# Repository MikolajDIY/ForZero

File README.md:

# ForZero

Sterownik fizycznego zestawu wskaźników Audi A4 B6, pozwalający wyświetlać telemetrię z Forza Horizon 6 przy użyciu STM32, CAN, USB i autorskiej aplikacji Qt.

ForZero powstał jako próba wykorzystania fizycznego zestawu wskaźników jako elementu stanowiska simracingowego. Projekt obejmuje rozpoznanie sposobów sterowania licznikiem, zaprojektowanie i uruchomienie własnej PCB, firmware mikrokontrolera oraz aplikację komputerową.

## Film prezentujący projekt

[Obejrzyj film na YouTube](https://www.youtube.com/watch?v=puXx0WQHfvw)

## Możliwości

- Wyświetlanie prędkości i obrotów silnika na fizycznym liczniku.
- Sterowanie wskazaniami poziomu paliwa i temperatury płynu chłodzącego.
- Obsługa wybranych kontrolek i komunikatów ostrzegawczych.
- Przybliżona symulacja stanów ABS, TCS i AIRBAG oraz temperatury płynu chłodzącego na podstawie dostępnej telemetrii.
- Odbiór danych UDP z gry i przesyłanie przetworzonych wartości do sterownika przez USB VCP.
- Pomiar opóźnień komunikacji na podstawie potwierdzeń wykonania ramek.
- Zerowanie prędkości i obrotów po 500 ms bez poprawnej ramki danych.

Gra nie udostępnia bezpośrednio wszystkich odwzorowywanych stanów. Algorytmy symulacji kontrolek i temperatury służą do przybliżonego odtworzenia ich zachowania; nie są modelami fizycznymi układów pojazdu.

## Jak to działa

Gra wysyła telemetrię przez UDP. Aplikacja Qt odbiera i parsuje pakiety, wykonuje dodatkową logikę oraz przesyła dane przez USB VCP do STM32F105. Mikrokontroler generuje sygnały elektryczne wymagane przez zestaw wskaźników.

Badany licznik wykorzystuje kilka różnych sposobów sterowania:

| Funkcja | Sposób sterowania |
| --- | --- |
| Obrotomierz | Ramki CAN |
| Prędkościomierz | Sygnał impulsowy o regulowanej częstotliwości |
| Poziom paliwa i temperatura | Emulacja rezystancji czujników |
| Wybrane kontrolki i ostrzeżenia | Sygnały logiczne 12 V |

Wskazania paliwa i temperatury skalibrowano eksperymentalnie. Zmierzone charakterystyki opracowano z wykorzystaniem interpolacji PCHIP w MATLAB-ie.

## Sprzęt

- Autorska dwuwarstwowa PCB zaprojektowana w KiCad.
- Mikrokontroler STM32F105 z jednoczesną obsługą USB i CAN.
- Transceiver CAN MCP2562 z osobnym zasilaniem interfejsu logicznego.
- Układy emulacji rezystancji oparte na potencjometrze cyfrowym MCP4661, wzmacniaczach operacyjnych i tranzystorach MOSFET.
- Tranzystorowe stopnie sterujące wejściami 12 V licznika.
- Złącze USB-C, zewnętrzne zasilanie 12 V i złącza Molex Micro-Fit 3.0.
- Zabezpieczenie ESD linii USB oraz bezpieczniki polimerowe na liniach zasilania.

## Oprogramowanie

### Aplikacja PC — C++ / Qt

Aplikacja ma trzy wątki: GUI, odbiór UDP oraz komunikację USB. Oddzielenie komunikacji od interfejsu użytkownika pozwala odbierać telemetrię i obsługiwać sterownik bez wykonywania tych operacji w wątku GUI.

Aplikacja odpowiada za parsowanie telemetrii, symulację wybranych wskazań, przygotowanie ramek dla sterownika i wyznaczanie statystyk opóźnień.

### Firmware — C / STM32 HAL

Firmware powstał w STM32CubeIDE z wykorzystaniem bibliotek HAL. Zadania w pętli głównej są wyzwalane zdarzeniowo lub w ustalonych interwałach:

| Sygnał | Aktualizacja |
| --- | --- |
| Prędkość i kontrolki | Po otrzymaniu nowych danych, gdy wartość się zmieni |
| Obroty silnika | Ramka CAN co 20 ms |
| Temperatura | Co 2 s |
| Poziom paliwa | Co 5 s, jeżeli odebrano nowe dane |

Własny protokół przesyłany przez USB VCP wykorzystuje znaczniki ramki, CRC8, numer sekwencyjny i potwierdzenie wykonania `Exec Ack`. Parser posiada timeout odbioru, a brak poprawnych danych przez 500 ms powoduje wyzerowanie prędkości i obrotów.

## Opóźnienia

Aplikacja mierzy czas przejścia danych w pętli PC–sterownik–PC (RTT), wykorzystując numery ramek i odpowiadające im potwierdzenia. Statystyki obejmują ostatnie 20 000 pomiarów.

W zestawach pomiarowych opisanych w dokumentacji średnie RTT zazwyczaj wynosiło poniżej 1 ms, a P99 poniżej 4 ms. W najbardziej skrajnym zarejestrowanym zestawie P99 osiągnął 17 ms. Są to wyniki przeprowadzonych testów, a nie gwarantowane limity czasowe.

**RTT nie jest pomiarem czasu od zdarzenia w grze do mechanicznego wychylenia wskazówki.** Poszczególne wyjścia mają własne okresy odświeżania, a licznik dodatkowo filtruje wskazania. Projekt pracuje jako system soft real-time.

## Zawartość repozytorium

| Folder | Zawartość |
| --- | --- |
| [Aplikacja Qt](Aplikacja%20Qt/) | Kod źródłowy aplikacji komputerowej |
| [Oprogramowanie sterownika](Oprogramowanie%20sterownika/) | Projekt firmware mikrokontrolera STM32 |
| [Schematy](Schematy/) | Materiały dotyczące części sprzętowej |
| [Obrazy](Obrazy/) | Zdjęcia i grafiki wykorzystywane w README |
| [Dokumentacja](ForZero_dokumentacja_v1.pdf) | Szczegółowa dokumentacja projektu |

## Uruchomienie

### Wymagania

- Zestaw wskaźników zgodny z egzemplarzem wykorzystanym w projekcie.
- Zmontowany sterownik ForZero, przewody połączeniowe i zasilanie 12 V.
- Przewód USB obsługujący transmisję danych.
- Komputer z aplikacją ForZero oraz Forza Horizon 6.
- Do samodzielnego zbudowania oprogramowania: środowisko Qt z kompilatorem C++ oraz STM32CubeIDE.

### Kolejność czynności

1. Przy odłączonym zasilaniu połącz sterownik z licznikiem zgodnie ze schematem połączeń w dokumentacji. Uwzględnij numerację pinów obu złączy licznika.
2. Zbuduj firmware z folderu [Oprogramowanie sterownika](Oprogramowanie%20sterownika/) i wgraj go do STM32. Programowanie jest możliwe przez USB z wykorzystaniem wbudowanego bootloadera.
3. Aby wejść w tryb bootloadera: naciśnij RESET, przytrzymując go naciśnij BOOT, zwolnij RESET, a następnie BOOT.
4. Po zaprogramowaniu uruchom sterownik w zwykłym trybie pracy i podłącz zasilanie zestawu.
5. Zbuduj i uruchom aplikację z folderu [Aplikacja Qt](Aplikacja%20Qt/), a następnie wybierz port COM sterownika.
6. Włącz wysyłanie telemetrii UDP w grze. Ustaw adres IP komputera odbierającego dane oraz port zgodny z konfiguracją aplikacji.
7. Uruchom jazdę i sprawdź odbiór danych oraz działanie wskazań.

<!-- Do uzupełnienia przed publikacją: sprawdzone wersje Qt i kompilatora, wymagane moduły Qt, dokładna procedura budowania, narzędzie do wgrywania przez USB oraz ustawienia telemetrii (IP, port i format pakietu). -->

## Zgodność i ograniczenia

- Projekt sprawdzono z licznikiem **Audi A4 B6 RB4 o oznaczeniu 8E0920900H**, z monochromatycznym wyświetlaczem FIS. Zgodność z innymi wersjami licznika nie została potwierdzona.
- W badanym egzemplarzu po rozpoczęciu jazdy wskazanie paliwa zmieniało się wyłącznie w dół, z tempem około jednej czwartej skali w ciągu 7–10 minut. Ograniczenie to utrudnia szybkie odwzorowanie zmian poziomu paliwa w grze.
- Kontrolki i komunikaty mają zachowanie wynikające z wewnętrznej logiki licznika. Symulacja ABS nie oznacza pełnej emulacji sterownika ABS ani niezależnego sterowania samą lampką ABS.
- Poziom 12 V dla wybranych wejść kontrolek przyjęto na podstawie testów używanego egzemplarza; nie potwierdzono go dokumentacją producenta.

## Dokumentacja

Dokumentacja projektu opisuje pinout licznika, schemat połączeń ze sterownikiem, układy elektroniczne, kalibrację wskazań, protokół USB oraz przeprowadzone testy.

<!-- Do uzupełnienia: dodaj względny link do PDF-u po ustaleniu jego nazwy i lokalizacji w repozytorium. -->

## Autor

M.Ratajczak — [MikolajDIY](https://github.com/MikolajDIY)

<!-- Przed publikacją określ zasady licencjonowania własnego kodu i projektu sprzętu. Zachowaj informacje licencyjne zależności i kodu generowanego. Dodaj odnośniki do wykorzystanych materiałów zewnętrznych. -->

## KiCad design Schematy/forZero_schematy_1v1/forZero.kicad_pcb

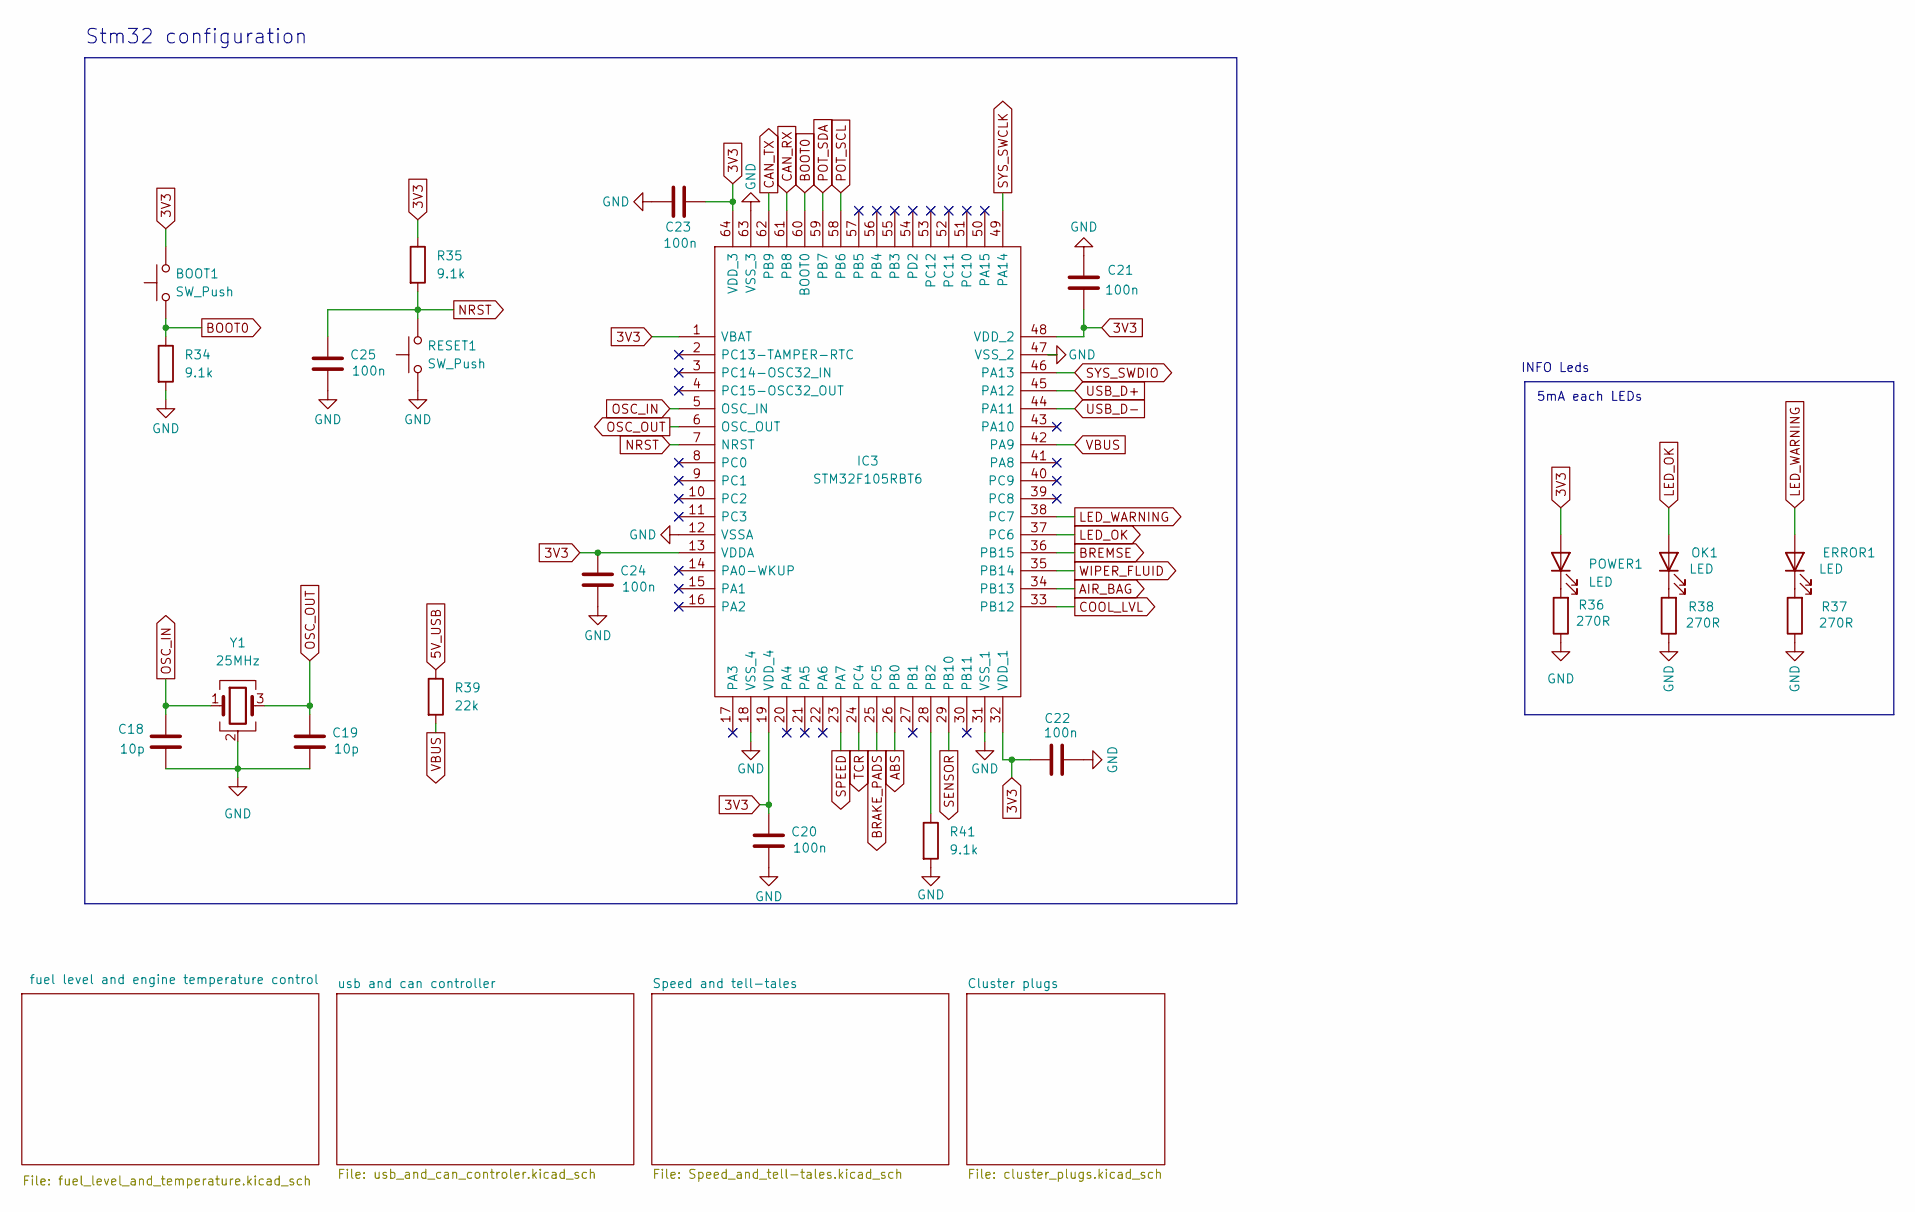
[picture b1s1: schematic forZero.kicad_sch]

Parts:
BOOT1: SW_Push; SW_SPST_PTS645Sx43SMTR92
C18, C19: 10p; C_0805_2012Metric_Pad1.18x1.45mm_HandSolder
C20, C21, C22, C23, C24, C25: 100n; C_0805_2012Metric_Pad1.18x1.45mm_HandSolder
ERROR1: LED; LED_0603_1608Metric_Pad1.05x0.95mm_HandSolder
IC3: STM32F105RBT6; QFP50P1200X1200X160-64N; Mouser Part Number 511-STM32F105RBT6
OK1: LED; LED_0603_1608Metric_Pad1.05x0.95mm_HandSolder
POWER1: LED; LED_0603_1608Metric_Pad1.05x0.95mm_HandSolder
R34, R35, R41: 9.1k; R_0805_2012Metric_Pad1.20x1.40mm_HandSolder
R36, R37, R38: 270R; R_0805_2012Metric_Pad1.20x1.40mm_HandSolder
R39: 22k; R_0805_2012Metric_Pad1.20x1.40mm_HandSolder
RESET1: SW_Push; SW_SPST_PTS645Sx43SMTR92
Y1: 25MHz; Crystal_SMD_3225-4Pin_3.2x2.5mm

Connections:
3V3: BOOT1.2, C20.1, C21.1, C22.1, C23.1, C24.1, IC3.1 (VBAT), IC3.13 (VDDA), IC3.19 (VDD_4), IC3.32 (VDD_1), IC3.48 (VDD_2), IC3.64 (VDD_3), POWER1.2 (A), R35.1; also elsewhere on the board
5V: R39.1; also elsewhere on the board
ABS: IC3.26 (PB0); also elsewhere on the board
AIR_BAG: IC3.34 (PB13); also elsewhere on the board
BOOT0: BOOT1.1, IC3.60 (BOOT0), R34.1; also elsewhere on the board
BRAKE_PADS: IC3.25 (PC5); also elsewhere on the board
BREMSE: IC3.36 (PB15); also elsewhere on the board
CAN_RX: IC3.61 (PB8); also elsewhere on the board
CAN_TX: IC3.62 (PB9); also elsewhere on the board
COOL_LVL: IC3.33 (PB12); also elsewhere on the board
GND: C18.2, C19.2, C20.2, C21.2, C22.2, C23.2, C24.2, C25.2, IC3.12 (VSSA), IC3.18 (VSS_4), IC3.31 (VSS_1), IC3.47 (VSS_2), IC3.63 (VSS_3), R34.2, R36.1, R37.1, R38.1, R41.2, RESET1.1, Y1.2 (G), Y1.4 (G); also elsewhere on the board
LED_OK: IC3.37 (PC6), OK1.2 (A); also elsewhere on the board
LED_WARNING: ERROR1.2 (A), IC3.38 (PC7); also elsewhere on the board
NRST: C25.1, IC3.7 (NRST), R35.2, RESET1.2; also elsewhere on the board
unnamed 33: ERROR1.1 (K), R37.2; also elsewhere on the board
unnamed: IC3.28 (PB2), R41.1
unnamed 46: OK1.1 (K), R38.2; also elsewhere on the board
unnamed 47: POWER1.1 (K), R36.2; also elsewhere on the board
OSC_IN: C18.1, IC3.5 (OSC_IN), Y1.1
OSC_OUT: C19.1, IC3.6 (OSC_OUT), Y1.3
POT_SCL: IC3.58 (PB6); also elsewhere on the board
POT_SDA: IC3.59 (PB7); also elsewhere on the board
SENSOR: IC3.29 (PB10); also elsewhere on the board
SPEED: IC3.23 (PA7); also elsewhere on the board
SYS_SWCLK: IC3.49 (PA14)
SYS_SWDIO: IC3.46 (PA13)
TCR: IC3.24 (PC4); also elsewhere on the board
USB_D+: IC3.45 (PA12); also elsewhere on the board
USB_D-: IC3.44 (PA11); also elsewhere on the board
VBUS: IC3.42 (PA9), R39.2
WIPER_FLUID: IC3.35 (PB14); also elsewhere on the board

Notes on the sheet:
INFO Leds
5mA each LEDs
Stm32 configuration

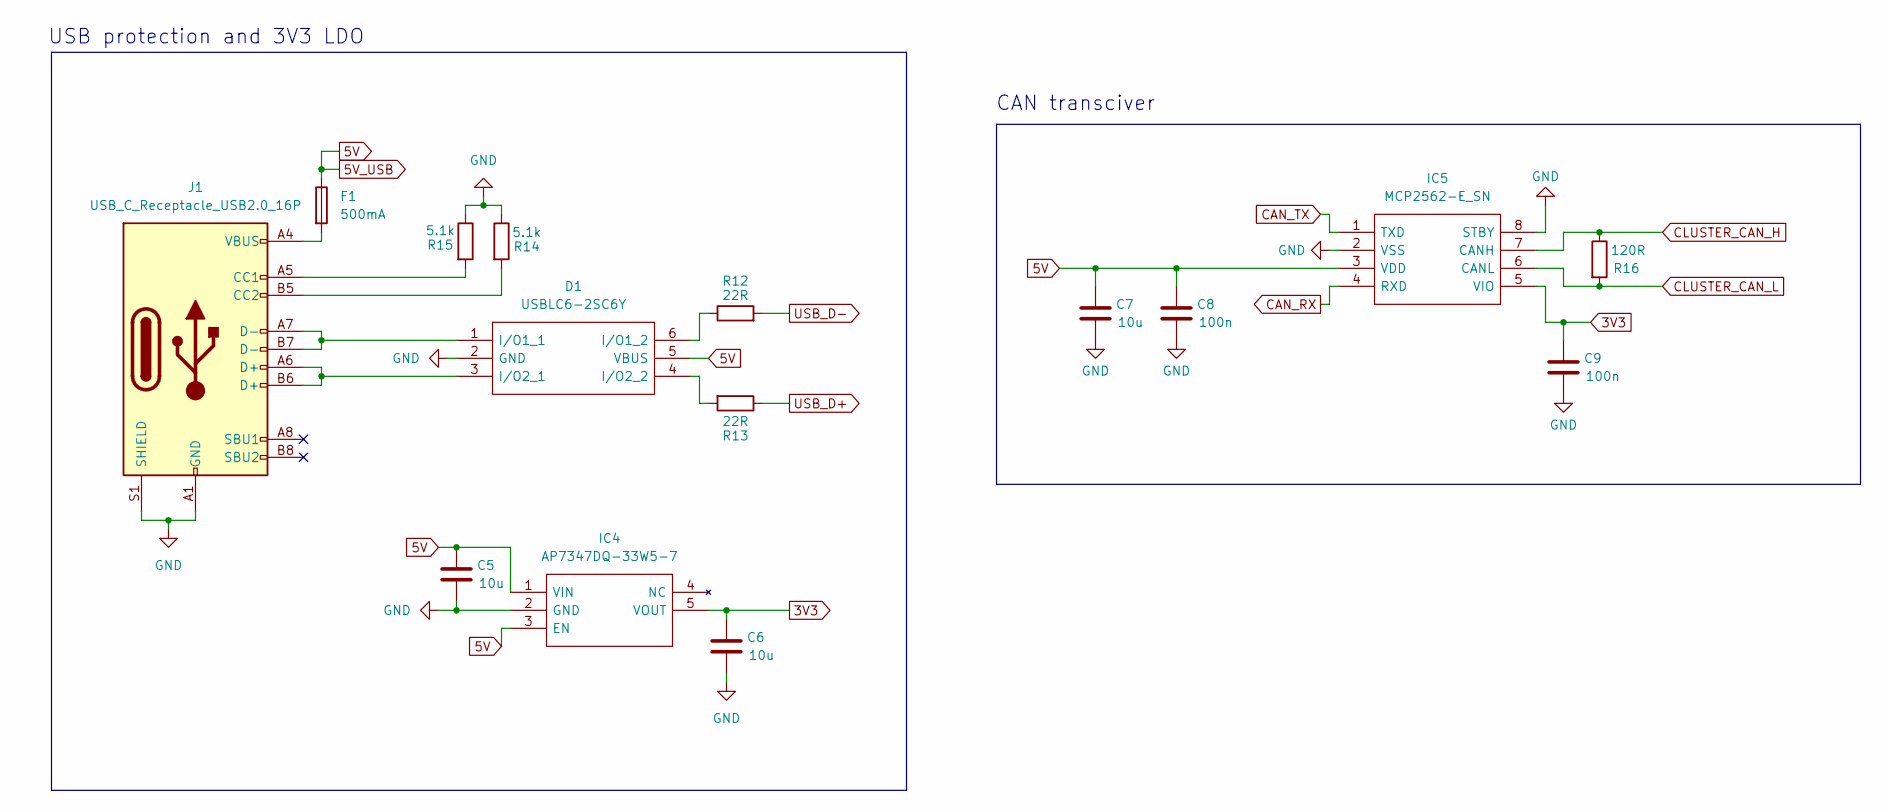
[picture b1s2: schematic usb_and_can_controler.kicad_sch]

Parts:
C5, C6, C7: 10u; C_0805_2012Metric_Pad1.18x1.45mm_HandSolder
C8, C9: 100n; C_0805_2012Metric_Pad1.18x1.45mm_HandSolder
D1: USBLC6-2SC6Y; SOT95P280X145-6N; Mouser Part Number 511-USBLC6-2SC6Y
F1: 500mA; Fuse_1206_3216Metric_Pad1.42x1.75mm_HandSolder
IC4: AP7347DQ-33W5-7; SOT95P280X145-5N; Mouser Part Number 621-AP7347DQ-33W5-7
IC5: MCP2562-E_SN; SOIC127P600X175-8N; Mouser Part Number 579-MCP2562-E/SN
J1: USB_C_Receptacle_USB2.0_16P; USB_C_Receptacle_GCT_USB4105-xx-A_16P_TopMnt_Horizontal
R12, R13: 22R; R_0805_2012Metric_Pad1.20x1.40mm_HandSolder
R14, R15: 5.1k; R_0805_2012Metric_Pad1.20x1.40mm_HandSolder
R16: 120R; R_0805_2012Metric_Pad1.20x1.40mm_HandSolder

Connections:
3V3: C6.1, C9.1, IC4.5 (VOUT), IC5.5 (VIO); also elsewhere on the board
5V: C5.1, C7.1, C8.1, D1.5 (VBUS), F1.1, IC4.1 (VIN), IC4.3 (EN), IC5.3 (VDD); also elsewhere on the board
CAN_RX: IC5.4 (RXD); also elsewhere on the board
CAN_TX: IC5.1 (TXD); also elsewhere on the board
CLUSTER_CAN_H: IC5.7 (CANH), R16.1; also elsewhere on the board
CLUSTER_CAN_L: IC5.6 (CANL), R16.2; also elsewhere on the board
GND: C5.2, C6.2, C7.2, C8.2, C9.2, D1.2 (GND), IC4.2 (GND), IC5.2 (VSS), IC5.8 (STBY), J1.A1 (GND), J1.A12 (GND), J1.B1 (GND), J1.B12 (GND), J1.S1 (SHIELD), R14.1, R15.1; also elsewhere on the board
unnamed: D1.1 (I/O1_1), J1.A7 (D-), J1.B7 (D-)
unnamed: D1.6 (I/O1_2), R12.1
unnamed: D1.3 (I/O2_1), J1.A6 (D+), J1.B6 (D+)
unnamed: D1.4 (I/O2_2), R13.2
unnamed: F1.2, J1.A4 (VBUS), J1.A9 (VBUS), J1.B4 (VBUS), J1.B9 (VBUS)
unnamed: J1.A5 (CC1), R15.2
unnamed: J1.B5 (CC2), R14.2
USB_D+: R13.1; also elsewhere on the board
USB_D-: R12.2; also elsewhere on the board

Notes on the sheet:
CAN transciver
USB protection and 3V3 LDO

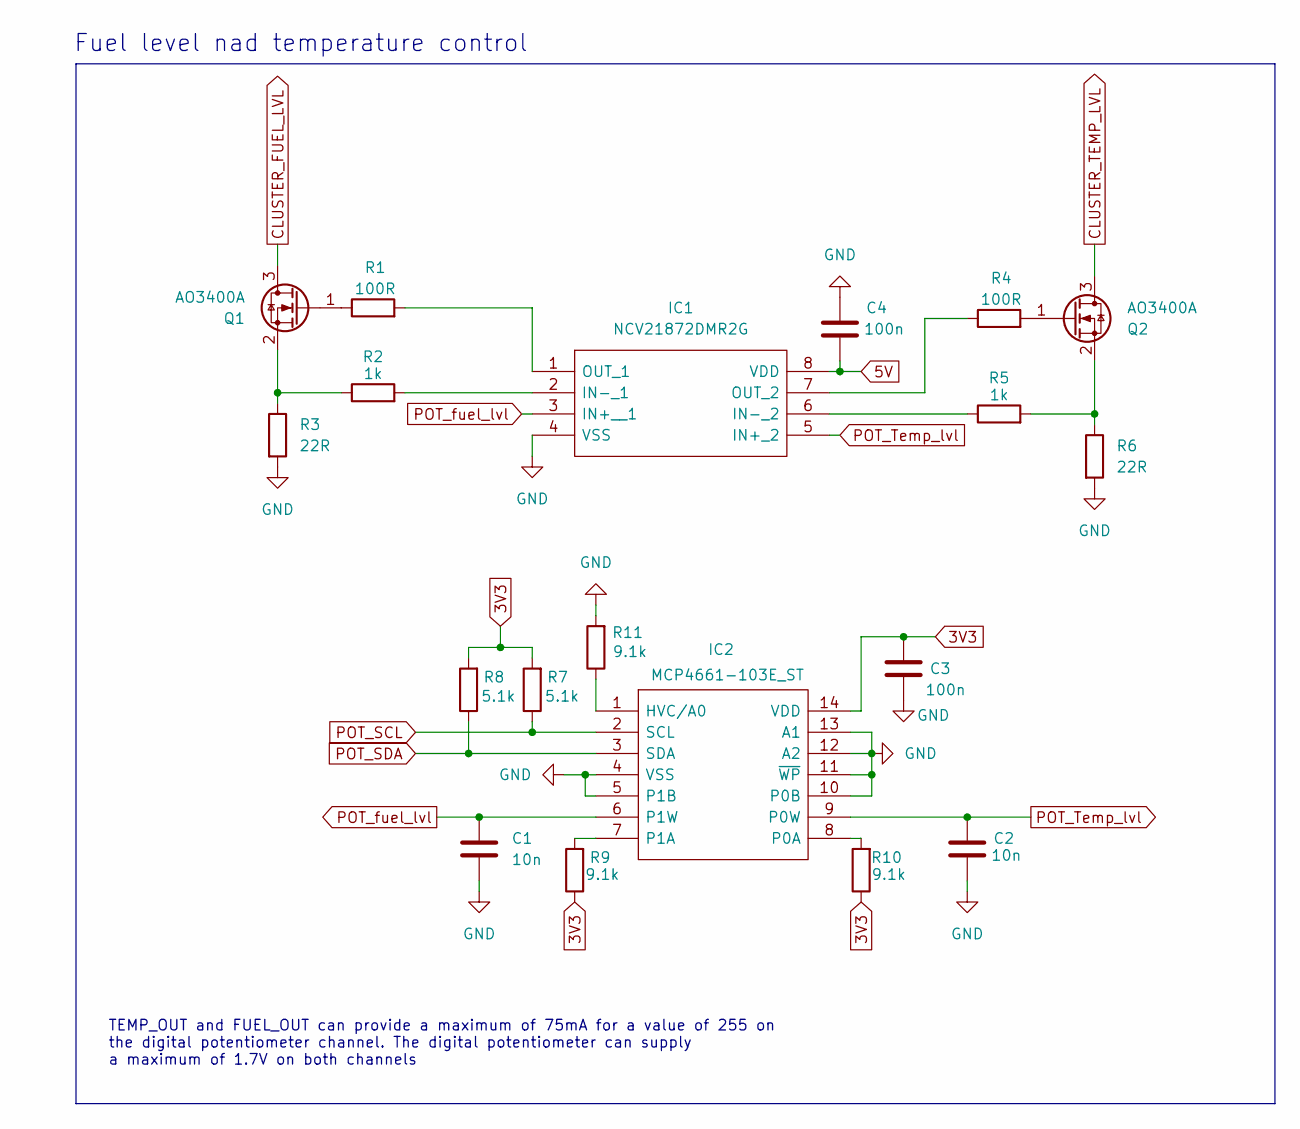
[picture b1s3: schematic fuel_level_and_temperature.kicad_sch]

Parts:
C1, C2: 10n; C_0805_2012Metric_Pad1.18x1.45mm_HandSolder
C3, C4: 100n; C_0805_2012Metric_Pad1.18x1.45mm_HandSolder
IC1: NCV21872DMR2G; SOP65P490X110-8N; Mouser Part Number 863-NCV21872DMR2G
IC2: MCP4661-103E_ST; SOP65P640X120-14N; Mouser Part Number 579-MCP4661-103E/ST
Q1, Q2: AO3400A; SOT-23
R1, R4: 100R; R_0805_2012Metric_Pad1.20x1.40mm_HandSolder
R2, R5: 1k; R_0805_2012Metric_Pad1.20x1.40mm_HandSolder
R3, R6: 22R; R_1206_3216Metric_Pad1.30x1.75mm_HandSolder
R7, R8: 5.1k; R_0805_2012Metric_Pad1.20x1.40mm_HandSolder
R9, R10, R11: 9.1k; R_0805_2012Metric_Pad1.20x1.40mm_HandSolder

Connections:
3V3: C3.1, IC2.14 (VDD), R7.2, R8.2, R9.1, R10.1; also elsewhere on the board
5V: C4.2, IC1.8 (VDD); also elsewhere on the board
CLUSTER_FUEL_LVL: Q1.3 (D); also elsewhere on the board
CLUSTER_TEMP_LVL: Q2.3 (D); also elsewhere on the board
GND: C1.2, C2.2, C3.2, C4.1, IC1.4 (VSS), IC2.4 (VSS), IC2.5 (P1B), IC2.10 (P0B), IC2.11 (~WP), IC2.12 (A2), IC2.13 (A1), R3.2, R6.2, R11.2; also elsewhere on the board
unnamed: IC1.2 (IN-_1), R2.2
unnamed: IC1.6 (IN-_2), R5.1
unnamed: IC1.1 (OUT_1), R1.2
unnamed: IC1.7 (OUT_2), R4.1
unnamed: IC2.1 (HVC/A0), R11.1
unnamed: IC2.8 (P0A), R10.2
unnamed: IC2.7 (P1A), R9.2
unnamed: Q1.1 (G), R1.1
unnamed: Q1.2 (S), R2.1, R3.1
unnamed: Q2.1 (G), R4.2
unnamed: Q2.2 (S), R5.2, R6.1
POT_SCL: IC2.2 (SCL), R7.1; also elsewhere on the board
POT_SDA: IC2.3 (SDA), R8.1; also elsewhere on the board
POT_Temp_lvl: C2.1, IC1.5 (IN+_2), IC2.9 (P0W)
POT_fuel_lvl: C1.1, IC1.3 (IN+__1), IC2.6 (P1W)

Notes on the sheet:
TEMP_OUT and FUEL_OUT can provide a maximum of 75mA for a value of 255 on the digital potentiometer channel. The digital potentiometer can supply a maximum of 1.7V on both channels
Fuel level nad temperature control

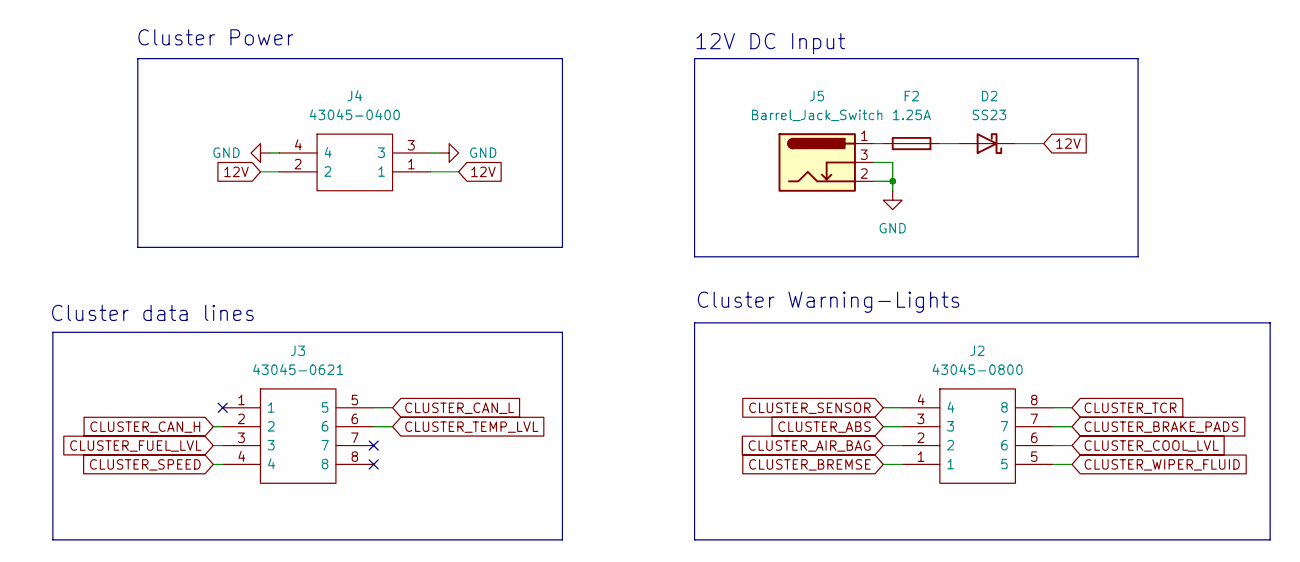
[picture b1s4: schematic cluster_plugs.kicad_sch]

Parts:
D2: SS23; D_SMA
F2: 1.25A; Fuse_1812_4532Metric_Pad1.30x3.40mm_HandSolder
J2: 43045-0800; 43045-08_00,01,02,10_; Mouser Part Number 538-43045-0800
J3: 43045-0621; 43045-06YY_212223; Mouser Part Number 538-43045-0621
J4: 43045-0400; 43045-04_00,01,02,10_; Mouser Part Number 538-43045-0400
J5: Barrel_Jack_Switch; BarrelJack_GCT_DCJ200-10-A_Horizontal

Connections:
12V: D2.1 (K), J4.1, J4.2; also elsewhere on the board
CLUSTER_ABS: J2.3; also elsewhere on the board
CLUSTER_AIR_BAG: J2.2; also elsewhere on the board
CLUSTER_BRAKE_PADS: J2.7; also elsewhere on the board
CLUSTER_BREMSE: J2.1; also elsewhere on the board
CLUSTER_CAN_H: J3.2; also elsewhere on the board
CLUSTER_CAN_L: J3.5; also elsewhere on the board
CLUSTER_COOL_LVL: J2.6; also elsewhere on the board
CLUSTER_FUEL_LVL: J3.3; also elsewhere on the board
CLUSTER_SENSOR: J2.4; also elsewhere on the board
CLUSTER_SPEED: J3.4; also elsewhere on the board
CLUSTER_TCR: J2.8; also elsewhere on the board
CLUSTER_TEMP_LVL: J3.6; also elsewhere on the board
CLUSTER_WIPER_FLUID: J2.5; also elsewhere on the board
GND: J4.3, J4.4, J5.2, J5.3; also elsewhere on the board
unnamed: D2.2 (A), F2.2
unnamed: F2.1, J5.1

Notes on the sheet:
Cluster data lines
Cluster Warning-Lights
Cluster Power
12V DC Input

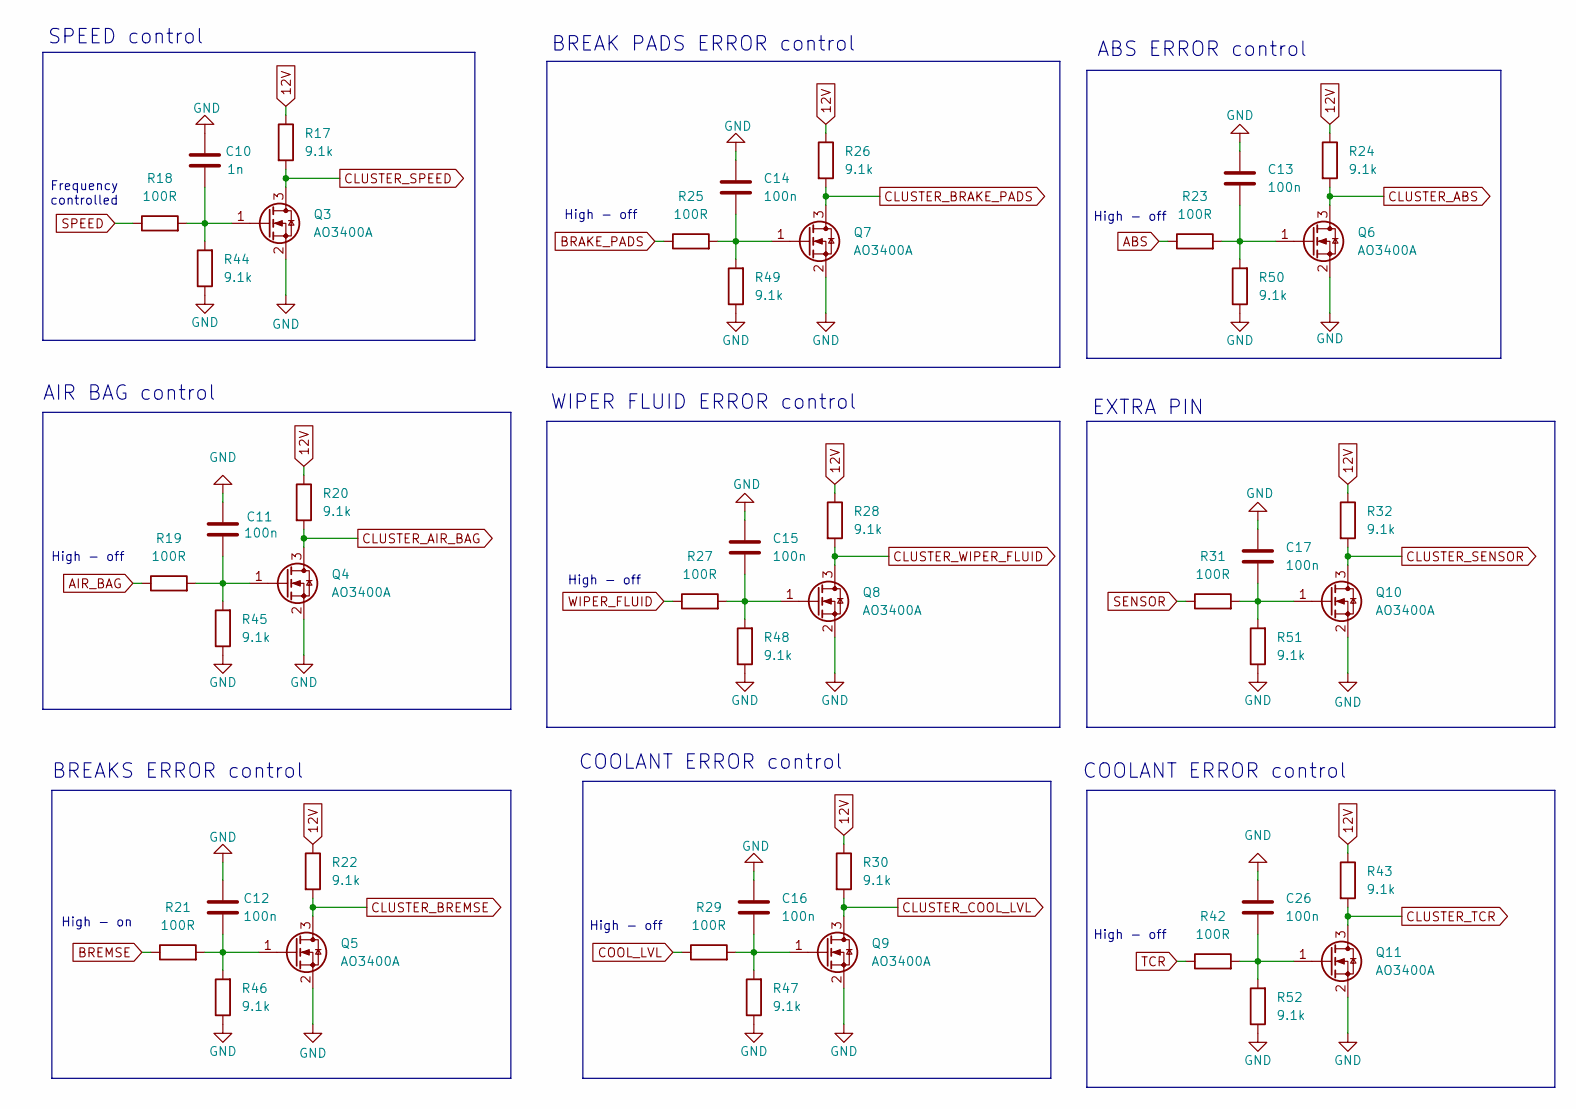
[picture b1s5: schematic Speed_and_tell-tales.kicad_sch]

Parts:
C10: 1n; C_0805_2012Metric_Pad1.18x1.45mm_HandSolder
C11, C12, C13, C14, C15, C16, C17, C26: 100n; C_0805_2012Metric_Pad1.18x1.45mm_HandSolder
Q3, Q4, Q5, Q6, Q7, Q8, Q9, Q10, Q11: AO3400A; SOT-23
R17, R20, R22, R24, R26, R28, R30, R32, R43, R44, R45, R46, R47, R48, R49, R50, R51, R52: 9.1k; R_0805_2012Metric_Pad1.20x1.40mm_HandSolder
R18, R19, R21, R23, R25, R27, R29, R31, R42: 100R; R_0805_2012Metric_Pad1.20x1.40mm_HandSolder

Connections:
12V: R17.1, R20.1, R22.1, R24.1, R26.1, R28.1, R30.1, R32.1, R43.1; also elsewhere on the board
ABS: R23.1; also elsewhere on the board
AIR_BAG: R19.1; also elsewhere on the board
BRAKE_PADS: R25.1; also elsewhere on the board
BREMSE: R21.1; also elsewhere on the board
CLUSTER_ABS: Q6.3 (D), R24.2; also elsewhere on the board
CLUSTER_AIR_BAG: Q4.3 (D), R20.2; also elsewhere on the board
CLUSTER_BRAKE_PADS: Q7.3 (D), R26.2; also elsewhere on the board
CLUSTER_BREMSE: Q5.3 (D), R22.2; also elsewhere on the board
CLUSTER_COOL_LVL: Q9.3 (D), R30.2; also elsewhere on the board
CLUSTER_SENSOR: Q10.3 (D), R32.2; also elsewhere on the board
CLUSTER_SPEED: Q3.3 (D), R17.2; also elsewhere on the board
CLUSTER_TCR: Q11.3 (D), R43.2; also elsewhere on the board
CLUSTER_WIPER_FLUID: Q8.3 (D), R28.2; also elsewhere on the board
COOL_LVL: R29.1; also elsewhere on the board
GND: C10.1, C11.2, C12.1, C13.1, C14.1, C15.1, C16.1, C17.1, C26.1, Q3.2 (S), Q4.2 (S), Q5.2 (S), Q6.2 (S), Q7.2 (S), Q8.2 (S), Q9.2 (S), Q10.2 (S), Q11.2 (S), R44.1, R45.1, R46.1, R47.1, R48.1, R49.1, R50.1, R51.1, R52.1; also elsewhere on the board
unnamed: C10.2, Q3.1 (G), R18.2, R44.2
unnamed: C11.1, Q4.1 (G), R19.2, R45.2
unnamed: C12.2, Q5.1 (G), R21.2, R46.2
unnamed: C13.2, Q6.1 (G), R23.2, R50.2
unnamed: C14.2, Q7.1 (G), R25.2, R49.2
unnamed: C15.2, Q8.1 (G), R27.2, R48.2
unnamed: C16.2, Q9.1 (G), R29.2, R47.2
unnamed: C17.2, Q10.1 (G), R31.2, R51.2
unnamed: C26.2, Q11.1 (G), R42.2, R52.2
SENSOR: R31.1; also elsewhere on the board
SPEED: R18.1; also elsewhere on the board
TCR: R42.1; also elsewhere on the board
WIPER_FLUID: R27.1; also elsewhere on the board

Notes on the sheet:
ABS ERROR control
COOLANT ERROR control
BREAK PADS ERROR control
High - off
BREAKS ERROR control
EXTRA PIN
AIR BAG control
SPEED control
Frequency controlled
WIPER FLUID ERROR control
High - on

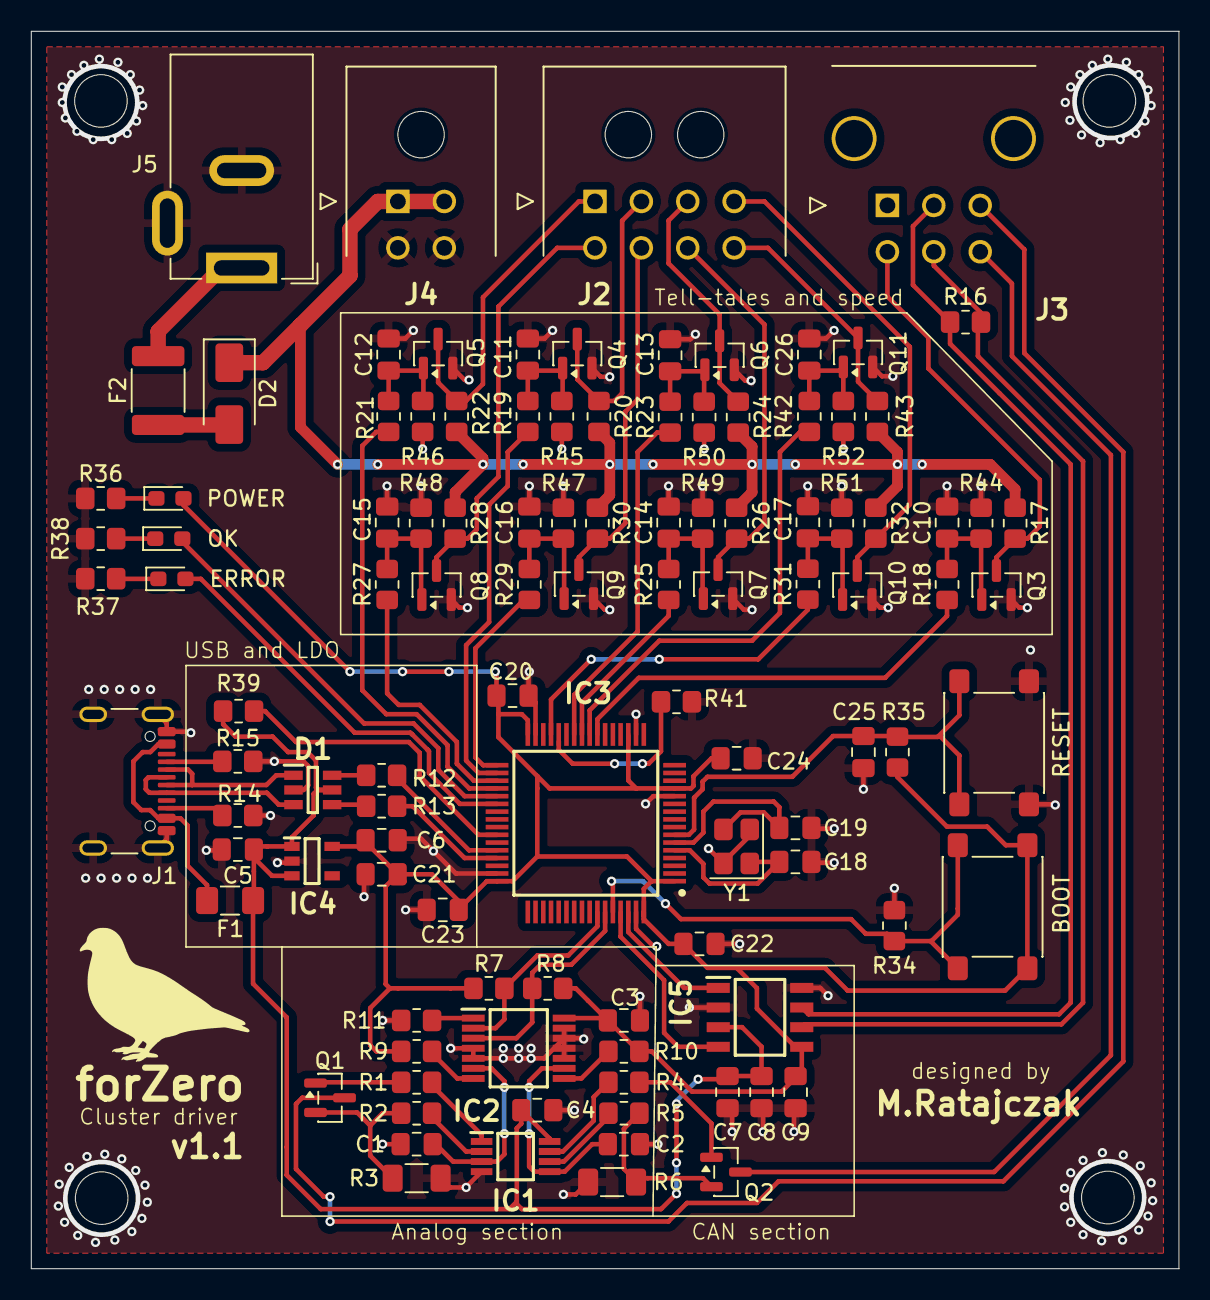
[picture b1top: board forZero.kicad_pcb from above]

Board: 2 copper layers, 74.2 x 80.0 mm, 107 parts (0 on the bottom side), 74 nets.

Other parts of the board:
BOOT: SW_Push; SW_SPST_PTS645Sx43SMTR92
ERROR: LED; LED_0603_1608Metric_Pad1.05x0.95mm_HandSolder
OK: LED; LED_0603_1608Metric_Pad1.05x0.95mm_HandSolder
POWER: LED; LED_0603_1608Metric_Pad1.05x0.95mm_HandSolder
RESET: SW_Push; SW_SPST_PTS645Sx43SMTR92

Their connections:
3V3: BOOT.2, POWER.2 (A); also elsewhere on the board
BOOT0: BOOT.1; also elsewhere on the board
GND: RESET.1; also elsewhere on the board
LED_OK: OK.2 (A); also elsewhere on the board
LED_WARNING: ERROR.2 (A); also elsewhere on the board
NRST: RESET.2; also elsewhere on the board
unnamed 33: ERROR.1 (K); also elsewhere on the board
unnamed 46: OK.1 (K); also elsewhere on the board
unnamed 47: POWER.1 (K); also elsewhere on the board

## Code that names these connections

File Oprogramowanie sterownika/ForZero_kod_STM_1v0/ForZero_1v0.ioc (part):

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Mcu.Name=STM32F105R(8-B-C)Tx
Mcu.Package=LQFP64
Mcu.UserName=STM32F105RBTx
PA11.Mode=Device_Only
PA11.Signal=USB_OTG_FS_DM
PA12.Mode=Device_Only
PA12.Signal=USB_OTG_FS_DP
PA7.Signal=S_TIM3_CH2
PB0.Signal=GPIO_Output
PB10.Signal=GPIO_Output
PB12.Signal=GPIO_Output
PB13.Signal=GPIO_Output
PB14.Signal=GPIO_Output
PB15.Signal=GPIO_Output
PB6.Mode=I2C
PB6.Signal=I2C1_SCL
PB7.Mode=I2C
PB7.Signal=I2C1_SDA
PB8.Mode=CAN_Activate
PB8.Signal=CAN1_RX
PB9.Mode=CAN_Activate
PB9.Signal=CAN1_TX
PC4.Signal=GPIO_Output
PC5.Signal=GPIO_Output
PC6.Signal=GPIO_Output
PC7.Signal=GPIO_Output
PD0-OSC_IN.Mode=HSE-External-Oscillator
PD0-OSC_IN.Signal=RCC_OSC_IN
PD1-OSC_OUT.Mode=HSE-External-Oscillator
PD1-OSC_OUT.Signal=RCC_OSC_OUT
RCC.HSEDivPLL=RCC_HSE_PREDIV_DIV5
RCC.HSE_VALUE=25000000
RCC.SYSCLKFreq_VALUE=72000000
RCC.SYSCLKSource=RCC_SYSCLKSOURCE_PLLCLK
board=custom

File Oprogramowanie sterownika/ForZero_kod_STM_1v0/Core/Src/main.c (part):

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
  // Kontrolki
  TellTales_Init();
 // Pin_Write(&LED_WARNING, GPIO_PIN_SET);

  start_cluster_test();
  /* USER CODE END 2 */
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	  if (HAL_GetTick() - last_time_usb_rx >= 500) {
		  __disable_irq();
		  rx_idx = 0; // Odrzucamy niekompletną paczkę
		  local_cluster.speed = 0;
		  local_cluster.rpm = 0;
		  local_cluster.engine_temp = 0;
		  local_cluster.indicators = 0x10;
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  HAL_GPIO_WritePin(GPIOB, GPIO_PIN_0|GPIO_PIN_10|GPIO_PIN_12|GPIO_PIN_13
                          |GPIO_PIN_14|GPIO_PIN_15, GPIO_PIN_RESET);

  /*Configure GPIO pins : PC4 PC5 PC6 PC7 */
  GPIO_InitStruct.Pin = GPIO_PIN_4|GPIO_PIN_5|GPIO_PIN_6|GPIO_PIN_7;
  GPIO_InitStruct.Mode = GPIO_MODE_OUTPUT_PP;
  GPIO_InitStruct.Pull = GPIO_NOPULL;
  GPIO_InitStruct.Speed = GPIO_SPEED_FREQ_LOW;
  HAL_GPIO_Init(GPIOC, &GPIO_InitStruct);

  /*Configure GPIO pins : PB0 PB10 PB12 PB13
                           PB14 PB15 */
  GPIO_InitStruct.Pin = GPIO_PIN_0|GPIO_PIN_10|GPIO_PIN_12|GPIO_PIN_13
                          |GPIO_PIN_14|GPIO_PIN_15;
  GPIO_InitStruct.Mode = GPIO_MODE_OUTPUT_PP;
  GPIO_InitStruct.Pull = GPIO_NOPULL;
  GPIO_InitStruct.Speed = GPIO_SPEED_FREQ_LOW;
  HAL_GPIO_Init(GPIOB, &GPIO_InitStruct);

  /* USER CODE BEGIN MX_GPIO_Init_2 */
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
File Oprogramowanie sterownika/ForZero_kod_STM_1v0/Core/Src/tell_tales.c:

/*
 * tell_tales.c
 *
 *  Created on: 10 sie 2026
 *      Author: rataj
 */
#include "tell_tales.h"

// LEDs on driver
const GPIO_Pin_t LED_OK = { .port = GPIOC, .pin = GPIO_PIN_6};
const GPIO_Pin_t LED_WARNING = { .port = GPIOC, .pin = GPIO_PIN_7};

// Tell-Tales
const GPIO_Pin_t TCR = { .port = GPIOC, .pin = GPIO_PIN_4};
const GPIO_Pin_t BRAKE_PADS = { .port = GPIOC, .pin = GPIO_PIN_5};
const GPIO_Pin_t ABS = { .port = GPIOB, .pin = GPIO_PIN_0};
const GPIO_Pin_t SENSOR = { .port = GPIOB, .pin = GPIO_PIN_10};
const GPIO_Pin_t COOL_LVL = { .port = GPIOB, .pin = GPIO_PIN_12};
const GPIO_Pin_t AIRBAG = { .port = GPIOB, .pin = GPIO_PIN_13};
const GPIO_Pin_t WIPER_FLUID = { .port = GPIOB, .pin = GPIO_PIN_14};
const GPIO_Pin_t BRAKES = { .port = GPIOB, .pin = GPIO_PIN_15};

// Speed
const GPIO_Pin_t SPEED = { .port = GPIOA, .pin = GPIO_PIN_7};

static const TellTale_Config_t TELL_TALES[8] ={
	{&ABS,			ABS_BIT, 				true},
	{&TCR, 			TCR_BIT, 				false},
	{&BRAKE_PADS, 	BRAKE_PADS_BIT, 		true},
	{&BRAKES, 		BRAKES_BIT, 			false},
	{&SENSOR,		SENSOR_BIT,				true},
	{&COOL_LVL,		COOL_LVL_BIT,			true},
	{&AIRBAG,		AIRBAG_BIT,				true},
	{&WIPER_FLUID,	WIPER_FLUID_BIT, 		true}
};

// Function used to set indicators state
void Pin_Write(const GPIO_Pin_t *gpio, GPIO_PinState state){
	HAL_GPIO_WritePin(gpio->port, gpio->pin, state);
}

void Send_TellTales(const uint8_t *indicators){
	uint8_t indi = *indicators;

	for(uint8_t i=0; i<8; i++){
		bool is_set = (indi & TELL_TALES[i].mask) != 0;

		if(TELL_TALES[i].inverted){
			is_set = !is_set;
		}

		GPIO_PinState state;
		state = is_set ? GPIO_PIN_SET : GPIO_PIN_RESET;
		Pin_Write(TELL_TALES[i].pin, state);
	}
}

void TellTales_Init(){
	  Pin_Write(&BRAKES, GPIO_PIN_RESET); // RESET - OFF
	  Pin_Write(&AIRBAG, GPIO_PIN_SET); // SET - OFF
	  Pin_Write(&ABS, GPIO_PIN_SET); // SET - OFF
	  Pin_Write(&TCR, GPIO_PIN_RESET); // RESET - OFF
	  Pin_Write(&COOL_LVL, GPIO_PIN_RESET); // SET - OFF
	  Pin_Write(&WIPER_FLUID, GPIO_PIN_SET); // SET - OFF
	  Pin_Write(&BRAKE_PADS, GPIO_PIN_SET); //SET - OFF
	  Pin_Write(&SENSOR, GPIO_PIN_RESET); // SET - OFF
}

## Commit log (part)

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2026-06-23 Dodanie pelnego pliku gitignore
2026-06-28 Pierwsze testy UART
2026-06-30 Dodano symulacje obwodu paliwa

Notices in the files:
Oprogramowanie sterownika/ForZero_kod_STM_1v0/Core/Src/main.c:
Copyright (c) 2026 STMicroelectronics.
All rights reserved.
This software is licensed under terms that can be found in the LICENSE file
